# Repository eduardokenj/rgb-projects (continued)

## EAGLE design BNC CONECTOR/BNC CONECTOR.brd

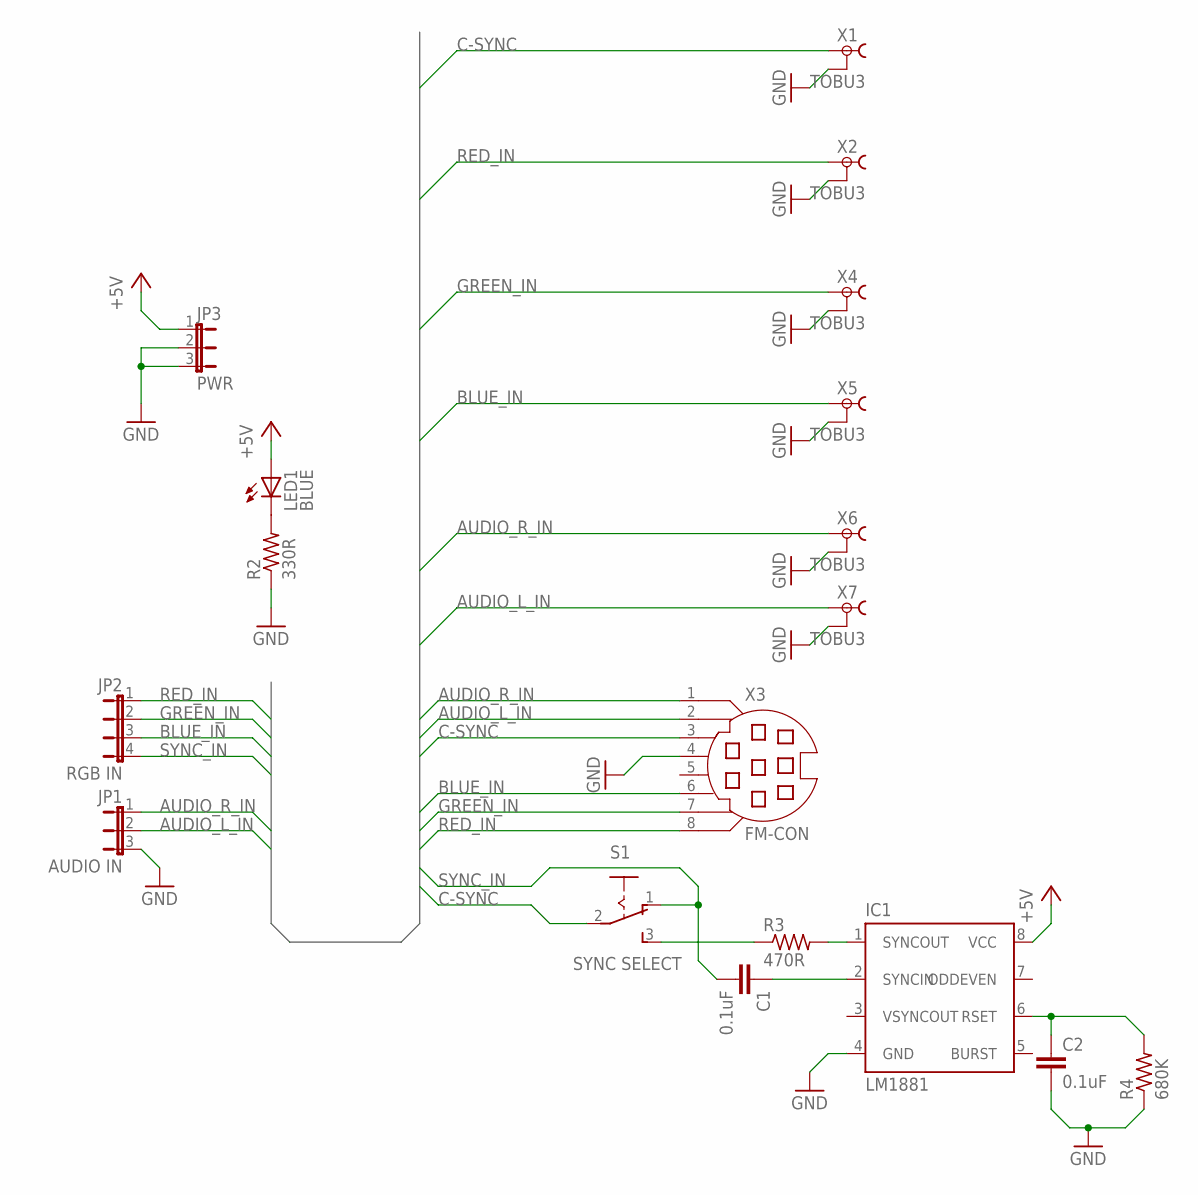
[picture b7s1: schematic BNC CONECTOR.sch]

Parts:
C1, C2: 0.1uF; C7.5B3
IC1: LM1881; DIL08
JP1: AUDIO IN; JP2
JP2: RGB IN; JP4
JP3: PWR; JP2
LED1: BLUE; LED5MM
R2: 330R; 0204/7
R3: 470R; 0204/7
R4: 680K; 0204/7
S1: SYNC SELECT; 255SB
X1, X2, X4, X5, X6, X7: TOBU3
X3: FM-CON; MDIN08SS

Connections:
+5V: IC1.8 (VCC), JP3.1, LED1.A
AUDIO_L_IN: JP1.2, X3.2, X7.1
AUDIO_R_IN: JP1.1, X3.1, X6.1
BLUE_IN: JP2.3, X3.6, X5.1
C-SYNC: S1.2, X1.1, X3.3
GND: C2.2, IC1.4 (GND), JP1.3, JP3.2, JP3.3, R2.1, R4.1, X1.2, X1.2@1 (2), X1.2@2 (2), X2.2, X2.2@1 (2), X2.2@2 (2), X3.4, X4.2, X4.2@1 (2), X4.2@2 (2), X5.2, X5.2@1 (2), X5.2@2 (2), X6.2, X6.2@1 (2), X6.2@2 (2), X7.2, X7.2@1 (2), X7.2@2 (2)
GREEN_IN: JP2.2, X3.7, X4.1
unnamed: R3.1, S1.3 (S)
unnamed: IC1.1 (SYNCOUT), R3.2
unnamed: LED1.K (C), R2.2
unnamed: C1.1, IC1.2 (SYNCIN)
unnamed: C2.1, IC1.6 (RSET), R4.2
RED_IN: JP2.1, X2.1, X3.8
SYNC_IN: C1.2, JP2.4, S1.1 (O)

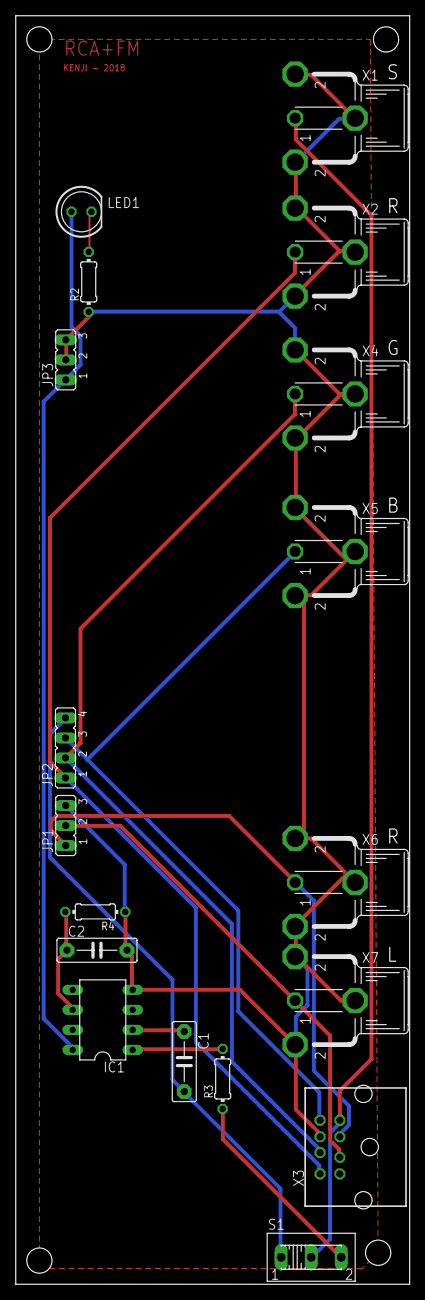
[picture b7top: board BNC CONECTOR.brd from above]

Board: 2 copper layers, 50.0 x 161.0 mm, 18 parts (0 on the bottom side), 14 nets.

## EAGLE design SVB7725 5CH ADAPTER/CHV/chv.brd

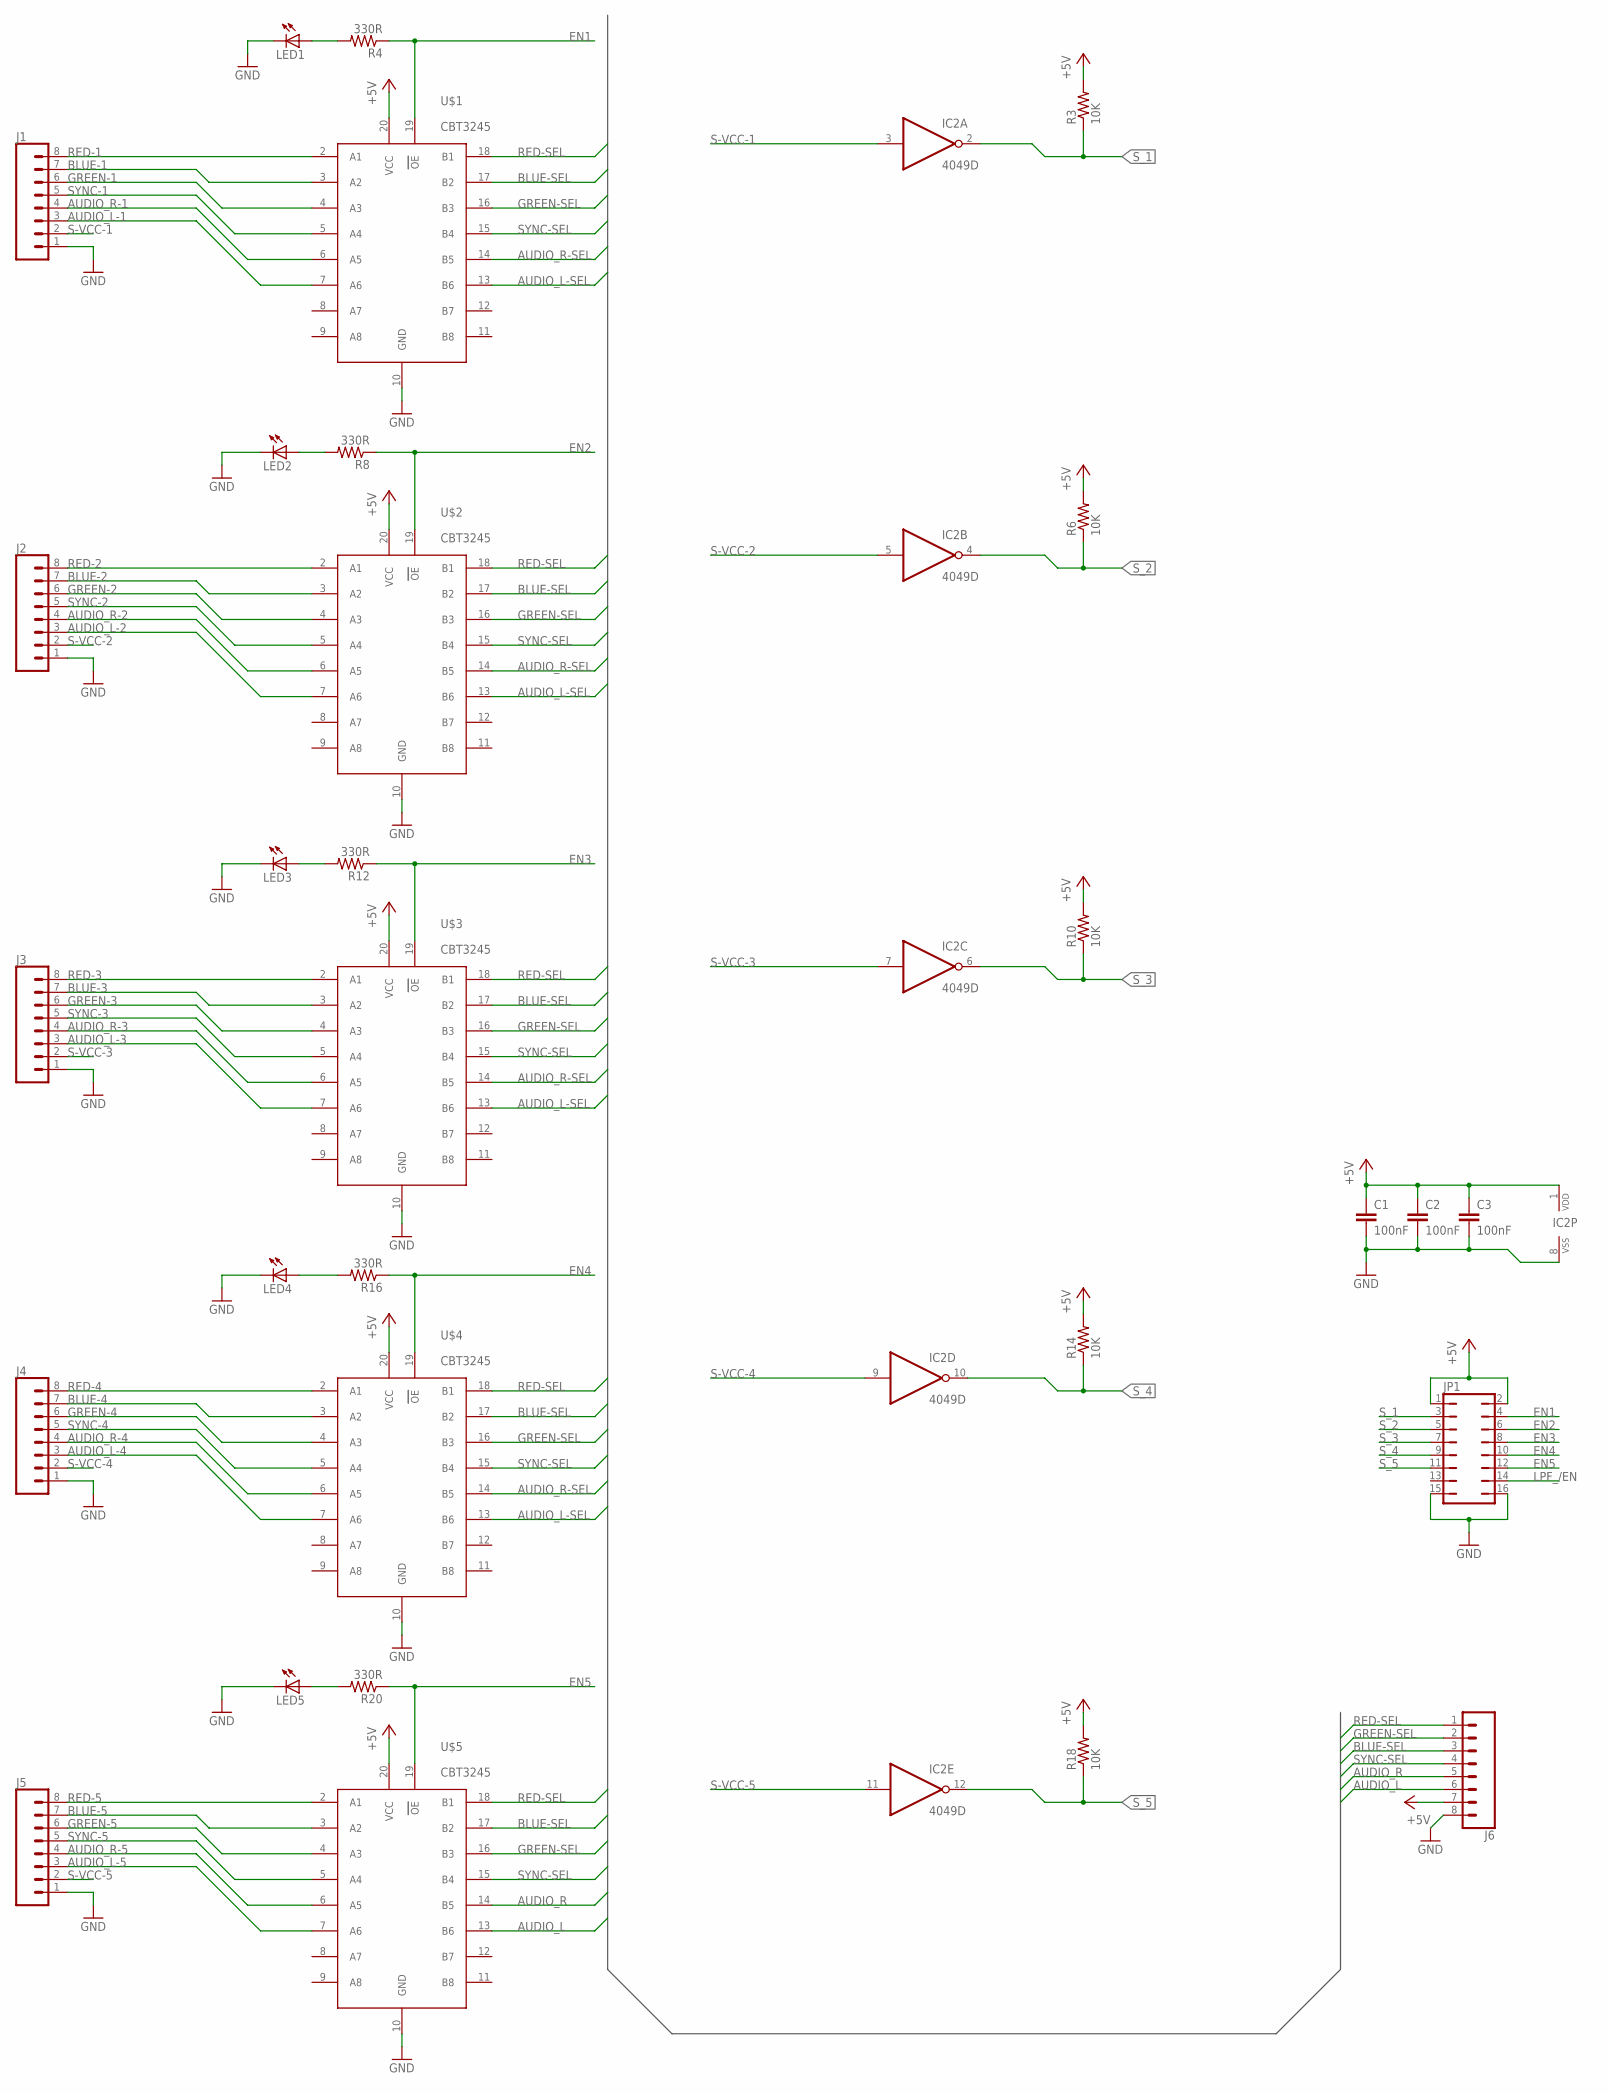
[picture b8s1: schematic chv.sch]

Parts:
C1, C2, C3: 100nF; C075-032X103
IC2: 4049D; SO16
J1, J2, J3, J4, J5, J6: CONN_08LONGPADS; 1X08_LONGPADS
JP1: JP8Q
LED1, LED2, LED3, LED4, LED5: LED5MM
R3, R6, R10, R14, R18: 10K; 0204V
R4, R8, R12, R16, R20: 330R; 0204V
U$1, U$2, U$3, U$4, U$5: CBT3245; SO20

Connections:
+5V: C1.1, C2.1, C3.1, IC2.1 (VDD), J6.7, JP1.1, JP1.2, R3.2, R6.2, R10.2, R14.2, R18.2, U$1.20 (VCC), U$2.20 (VCC), U$3.20 (VCC), U$4.20 (VCC), U$5.20 (VCC)
AUDIO_L: J6.6, U$5.13 (B6)
AUDIO_L-1: J1.3, U$1.7 (A6)
AUDIO_L-2: J2.3, U$2.7 (A6)
AUDIO_L-3: J3.3, U$3.7 (A6)
AUDIO_L-4: J4.3, U$4.7 (A6)
AUDIO_L-5: J5.3, U$5.7 (A6)
AUDIO_L-SEL: U$1.13 (B6), U$2.13 (B6), U$3.13 (B6), U$4.13 (B6)
AUDIO_R: J6.5, U$5.14 (B5)
AUDIO_R-1: J1.4, U$1.6 (A5)
AUDIO_R-2: J2.4, U$2.6 (A5)
AUDIO_R-3: J3.4, U$3.6 (A5)
AUDIO_R-4: J4.4, U$4.6 (A5)
AUDIO_R-5: J5.4, U$5.6 (A5)
AUDIO_R-SEL: U$1.14 (B5), U$2.14 (B5), U$3.14 (B5), U$4.14 (B5)
BLUE-1: J1.7, U$1.3 (A2)
BLUE-2: J2.7, U$2.3 (A2)
BLUE-3: J3.7, U$3.3 (A2)
BLUE-4: J4.7, U$4.3 (A2)
BLUE-5: J5.7, U$5.3 (A2)
BLUE-SEL: J6.3, U$1.17 (B2), U$2.17 (B2), U$3.17 (B2), U$4.17 (B2), U$5.17 (B2)
EN1: JP1.4, R4.1, U$1.19 (OE)
EN2: JP1.6, R8.1, U$2.19 (OE)
EN3: JP1.8, R12.1, U$3.19 (OE)
EN4: JP1.10, R16.1, U$4.19 (OE)
EN5: JP1.12, R20.1, U$5.19 (OE)
GND: C1.2, C2.2, C3.2, IC2.8 (VSS), J1.1, J2.1, J3.1, J4.1, J5.1, J6.8, JP1.15, JP1.16, LED1.K (C), LED2.K (C), LED3.K (C), LED4.K (C), LED5.K (C), U$1.10 (GND), U$2.10 (GND), U$3.10 (GND), U$4.10 (GND), U$5.10 (GND)
GREEN-1: J1.6, U$1.4 (A3)
GREEN-2: J2.6, U$2.4 (A3)
GREEN-3: J3.6, U$3.4 (A3)
GREEN-4: J4.6, U$4.4 (A3)
GREEN-5: J5.6, U$5.4 (A3)
GREEN-SEL: J6.2, U$1.16 (B3), U$2.16 (B3), U$3.16 (B3), U$4.16 (B3), U$5.16 (B3)
LPF_/EN: JP1.14
unnamed: LED1.A, R4.2
unnamed: LED2.A, R8.2
unnamed: LED3.A, R12.2
unnamed: LED4.A, R16.2
unnamed: LED5.A, R20.2
RED-1: J1.8, U$1.2 (A1)
RED-2: J2.8, U$2.2 (A1)
RED-3: J3.8, U$3.2 (A1)
RED-4: J4.8, U$4.2 (A1)
RED-5: J5.8, U$5.2 (A1)
RED-SEL: J6.1, U$1.18 (B1), U$2.18 (B1), U$3.18 (B1), U$4.18 (B1), U$5.18 (B1)
S-VCC-1: IC2.3 (I), J1.2
S-VCC-2: IC2.5 (I), J2.2
S-VCC-3: IC2.7 (I), J3.2
S-VCC-4: IC2.9 (I), J4.2
S-VCC-5: IC2.11 (I), J5.2
SYNC-1: J1.5, U$1.5 (A4)
SYNC-2: J2.5, U$2.5 (A4)
SYNC-3: J3.5, U$3.5 (A4)
SYNC-4: J4.5, U$4.5 (A4)
SYNC-5: J5.5, U$5.5 (A4)
SYNC-SEL: J6.4, U$1.15 (B4), U$2.15 (B4), U$3.15 (B4), U$4.15 (B4), U$5.15 (B4)
S_1: IC2.2 (O), JP1.3, R3.1
S_2: IC2.4 (O), JP1.5, R6.1
S_3: IC2.6 (O), JP1.7, R10.1
S_4: IC2.10 (O), JP1.9, R14.1
S_5: IC2.12 (O), JP1.11, R18.1

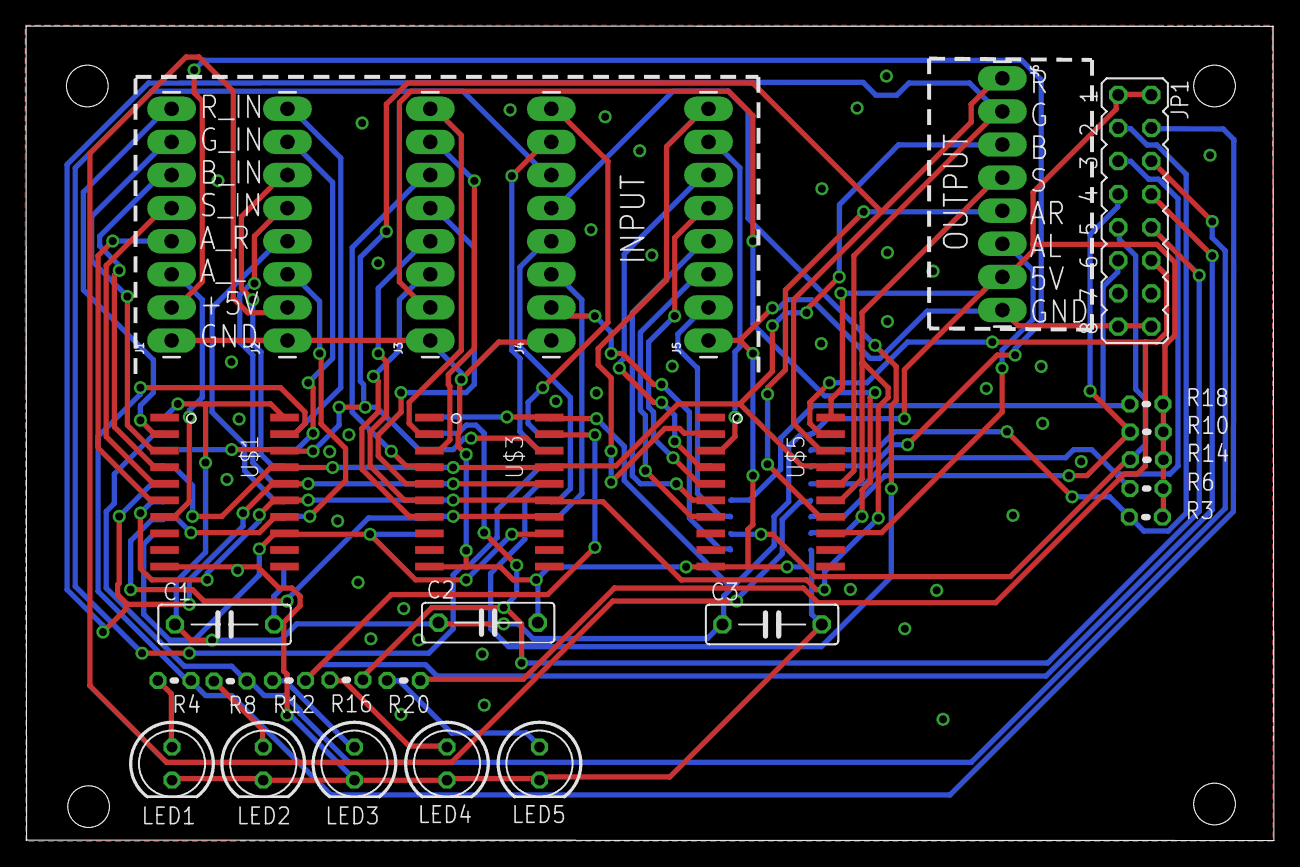
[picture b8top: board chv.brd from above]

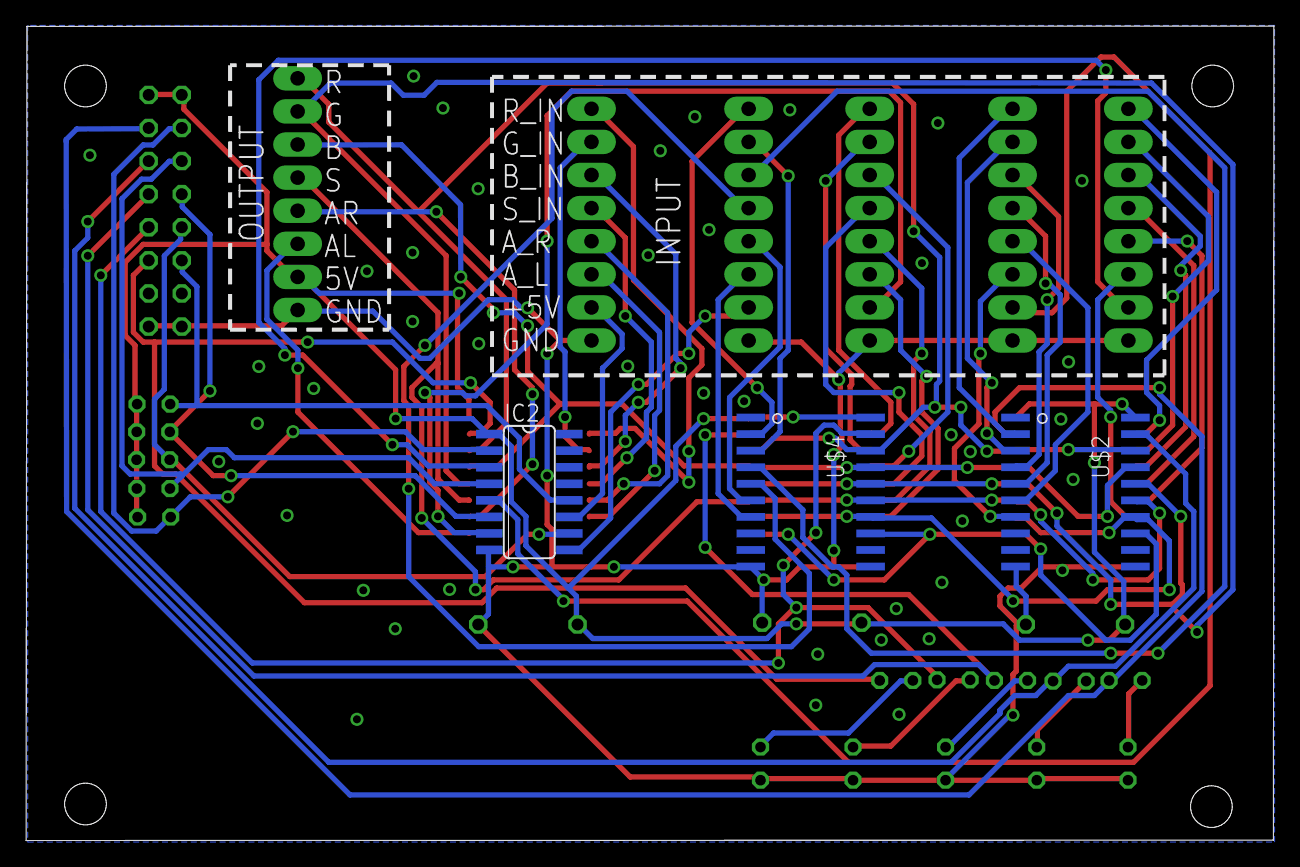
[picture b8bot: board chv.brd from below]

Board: 2 copper layers, 95.8 x 62.5 mm, 31 parts (3 on the bottom side), 60 nets.

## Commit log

2018-03-04 Upload REV1 boards
2018-03-04 Upload REV1 boards - SCART MODULAR
